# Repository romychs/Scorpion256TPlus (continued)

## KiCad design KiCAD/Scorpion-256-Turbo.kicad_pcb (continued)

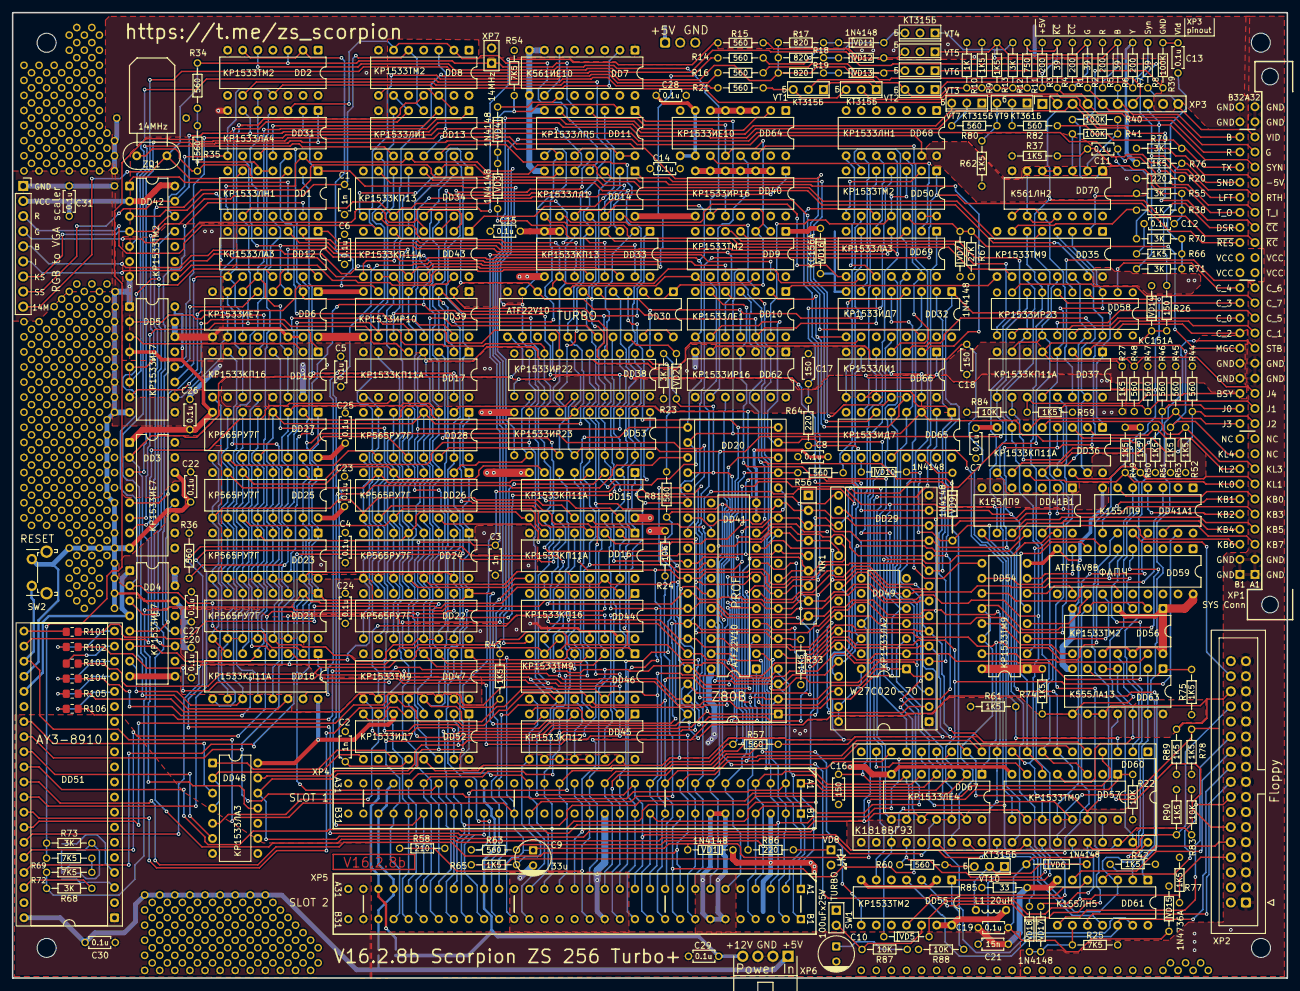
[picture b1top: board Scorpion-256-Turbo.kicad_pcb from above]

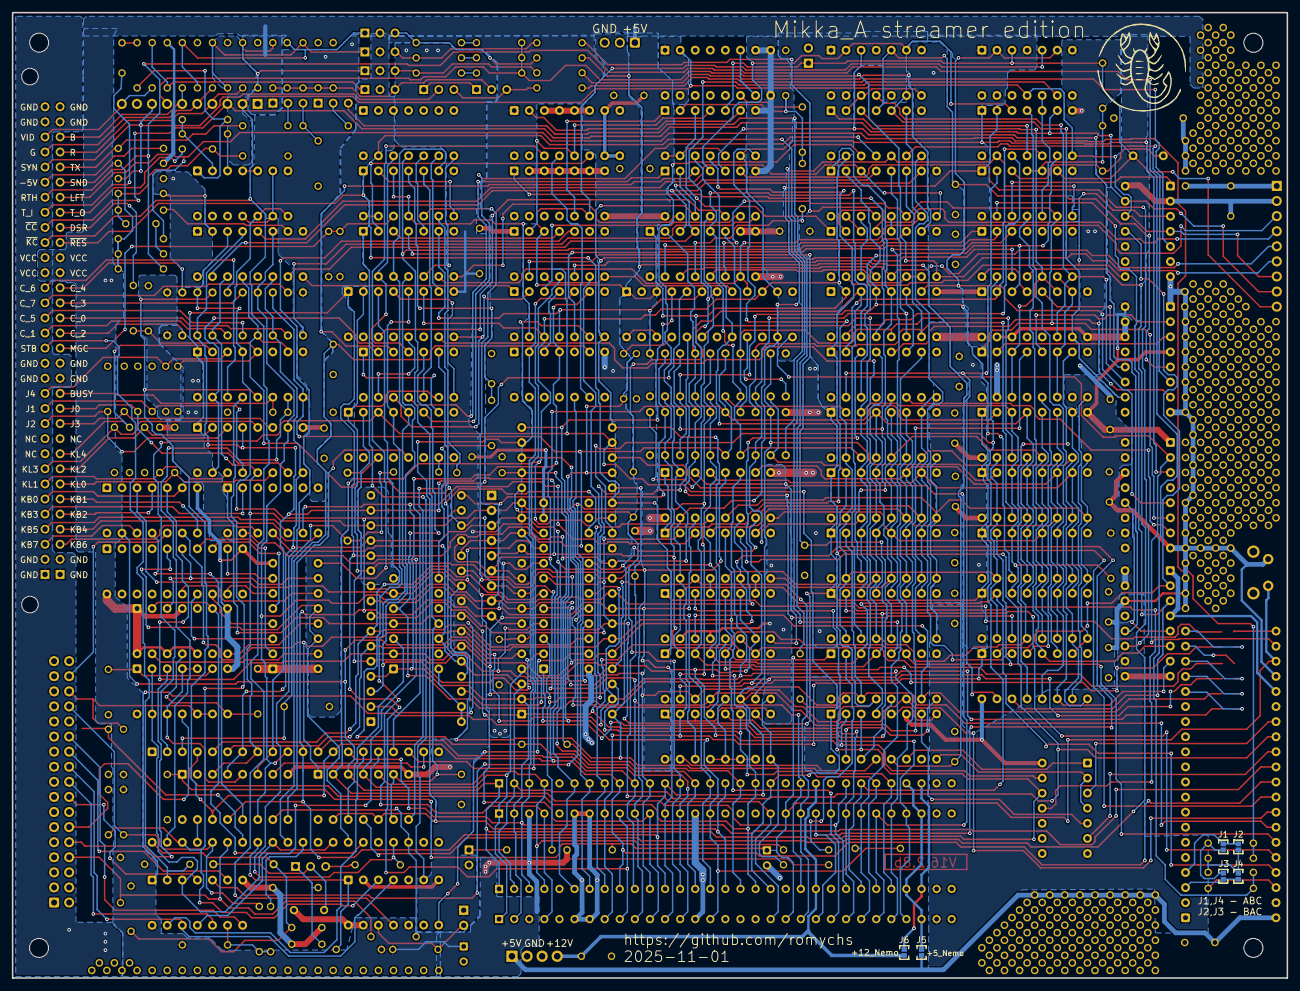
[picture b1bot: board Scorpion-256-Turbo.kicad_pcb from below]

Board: 2 copper layers, 214.6 x 162.6 mm, 240 parts (6 on the bottom side), 346 nets.

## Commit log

2021-02-08 Fixed top view of PCB
2021-02-08 New B/W PCB Image
2021-02-21 Исправления, замеченные в процессе сборки платы
2021-11-23 Fixed GAL PPL FDC connection. Extended power poligons on PCB.
2022-01-18 Gerber regenerated in new version of EasyEDA
2022-03-17 BOM, ROMs, GALs
2022-04-11 Fixed printer strobe sygnal
2022-04-26 Audio quality fix and removed extra vias
2022-05-25 Fix DSR sygnal schematics
2022-06-01 Cosmetic changer on schematics
2022-06-05 v16.2.4
2022-06-05 Fixed BOM to v16.2.4
2022-06-05 Fixed references if readme file
2022-06-05 Fixed readme file
2022-06-06 Renumbered diodes
2022-06-14 Jumpers to select ABC BAC AY channels layout
2022-08-12 Resistors added to protect AY I/O port pins from overload
2022-08-24 Silkscreen Bug Fixing in readme.
2022-09-12 Fixed footprint for transistors
2022-09-12 Updated BOM and fixed silk for some diodes
2022-09-15 Silk correction for zener diodes, and NR1
2022-09-19 Fixed BOM
2022-10-01 Small schematics and BOM fixes
2022-10-30 v16.2.7 Additional power connectors
2022-10-30 Readme fix
2022-11-07 Scorpion ROM from Mikka_A
2022-11-08 System connector DIN-41612 type can be used
2022-11-18 Firxed RGB color output sygnals
2024-05-05 Mikka_A Streaming Edition
2024-05-05 fix readme references
2024-05-17 ProfROM from LW added
2025-10-26 555IE10,IR16 -> 1533
2025-10-26 DD61-555->155
2025-11-04 Project ported to KiCAD from EasyEDA-STD
2025-12-08 Fix diode footprint. Fix gerbers
